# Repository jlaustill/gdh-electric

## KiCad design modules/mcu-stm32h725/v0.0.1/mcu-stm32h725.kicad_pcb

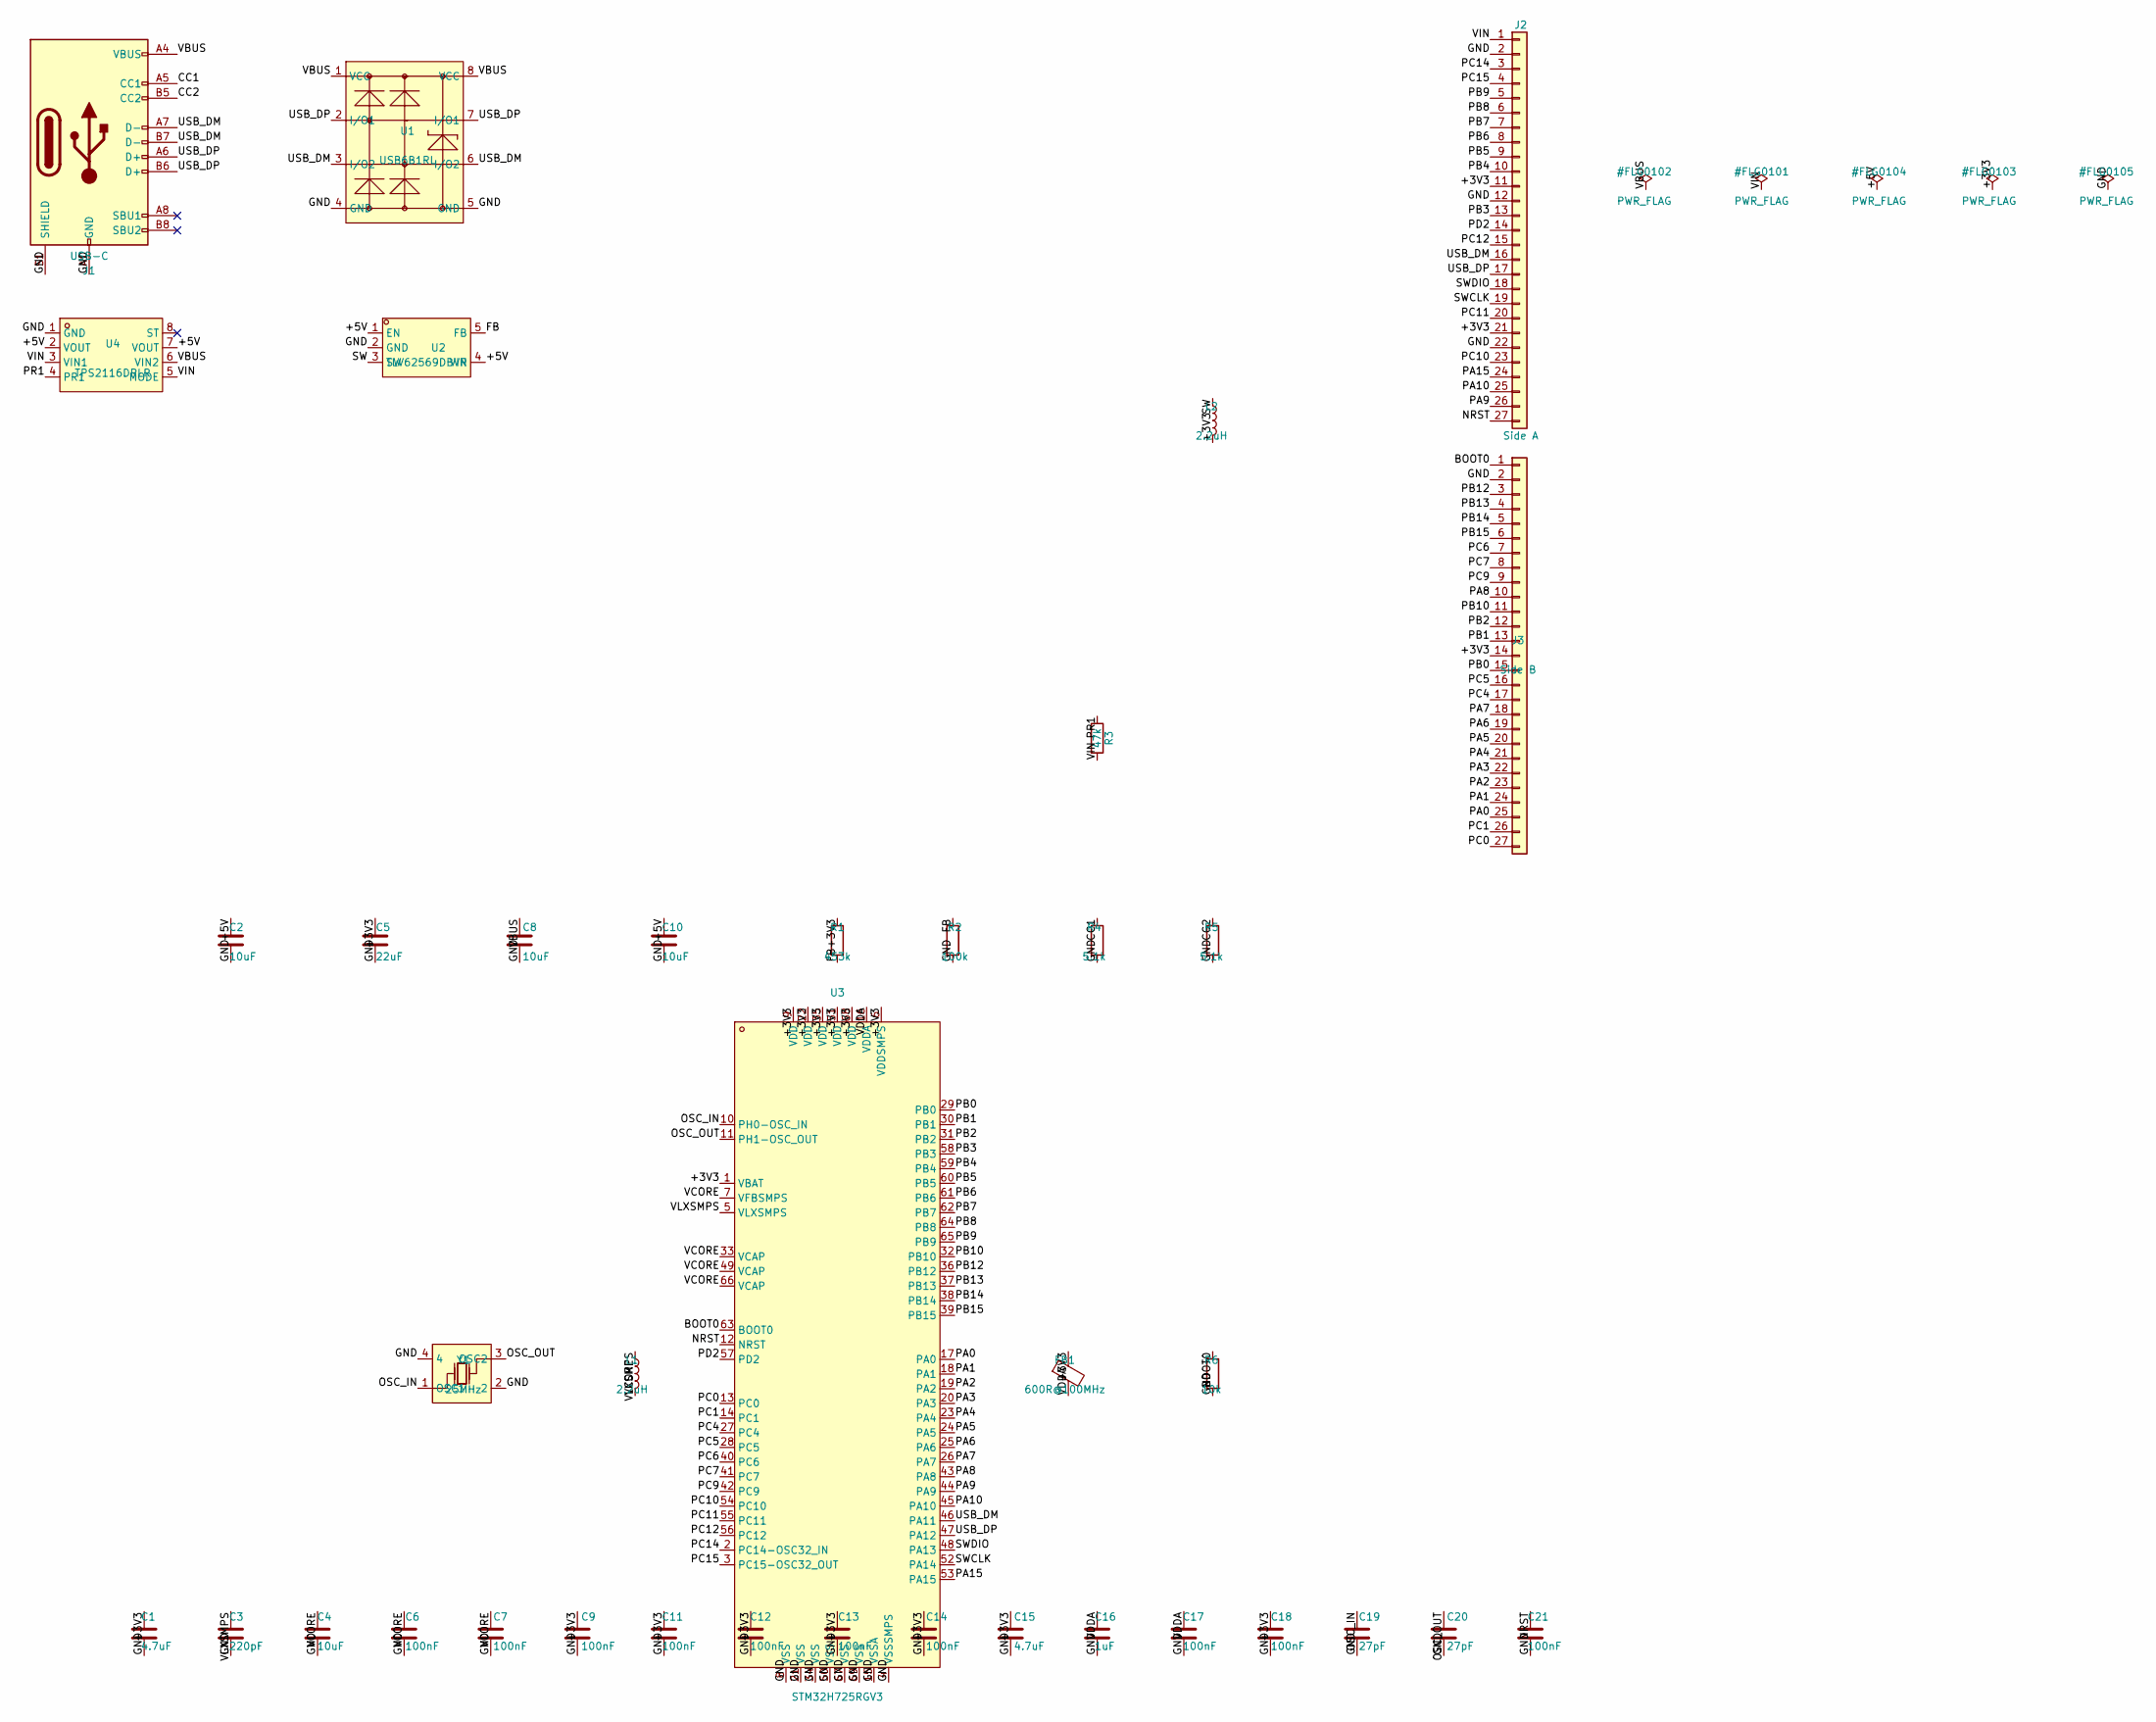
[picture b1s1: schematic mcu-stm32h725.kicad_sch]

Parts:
C1, C15: 4.7uF; C_0805_2012Metric
C2, C4, C8, C10: 10uF; C_0805_2012Metric
C3: 220pF; C_0402_1005Metric
C5: 22uF; C_0805_2012Metric
C6, C7, C9, C11, C12, C13, C14, C17, C18, C21: 100nF; C_0402_1005Metric
C16: 1uF; C_0805_2012Metric
C19, C20: 27pF; C_0402_1005Metric
FB1: 600R@100MHz; L_0805_2012Metric
J1: USB-C; USB-C_HYP_TC020-24LB02R_C23376530
J2: Side A; Castellation_1x27_P2.54mm_Edge
J3: Side B; Castellation_1x27_P2.54mm_Edge
L1, L2: 2.2uH; L_1210_3225Metric
R1: 453k; R_0603_1608Metric
R2: 100k; R_0603_1608Metric
R3: 47k; R_0603_1608Metric
R4, R5: 5.1k; R_0603_1608Metric
R6: 10k; R_0603_1608Metric
U1: USB6B1RL; SOIC-8_L4.9-W3.9-P1.27-LS6.0-BL
U2: TLV62569DBVR; SOT-23-5_L3.0-W1.7-P0.95-LS2.8-BR
U3: STM32H725RGV3; QFN-68_L8.0-W8.0-P0.40-BL-EP6.4
U4: TPS2116DRLR; SOT-583-8_L2.1-W1.6-P0.50-LS1.6-BL
Y1: 25MHz; CRYSTAL-SMD_4P-L3.2-W2.5-BL

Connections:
/+3V3: C1.1, C5.1, C9.1, C11.1, C12.1, C13.1, C14.1, C15.1, C18.1, FB1.1, J2.11, J2.21, J3.14, L2.2, R1.1, U3.1 (VBAT), U3.6 (VDDSMPS), U3.9 (VDD), U3.22 (VDD), U3.35 (VDD), U3.51 (VDD), U3.68 (VDD)
/+5V: C2.1, C10.1, U2.1 (EN), U2.4 (VIN), U4.2 (VOUT), U4.7 (VOUT)
/BOOT0: J3.1, R6.1, U3.63 (BOOT0)
/CC1: J1.A5 (CC1), R4.1
/CC2: J1.B5 (CC2), R5.1
/FB: R1.2, R2.1, U2.5 (FB)
/GND: C1.2, C2.2, C3.2, C4.2, C5.2, C6.2, C7.2, C8.2, C9.2, C10.2, C11.2, C12.2, C13.2, C14.2, C15.2, C16.2, C17.2, C18.2, C19.2, C20.2, C21.2, J1.A1 (GND), J1.A12 (GND), J1.B1 (GND), J1.B12 (GND), J1.S1 (SHIELD), J2.2, J2.12, J2.22, J3.2, R2.2, R4.2, R5.2, R6.2, U1.4 (GND), U1.5 (GND), U2.2 (GND), U3.4 (VSSSMPS), U3.8 (VSS), U3.15 (VSSA), U3.21 (VSS), U3.34 (VSS), U3.50 (VSS), U3.67 (VSS), U3.69 (VSS), U4.1 (GND), Y1.2, Y1.4
/NRST: C21.1, J2.27, U3.12 (NRST)
/OSC_IN: C19.1, U3.10 (PH0-OSC_IN), Y1.1 (OSC1)
/OSC_OUT: C20.1, U3.11 (PH1-OSC_OUT), Y1.3 (OSC2)
/PA0: J3.25, U3.17 (PA0)
/PA1: J3.24, U3.18 (PA1)
/PA2: J3.23, U3.19 (PA2)
/PA3: J3.22, U3.20 (PA3)
/PA4: J3.21, U3.23 (PA4)
/PA5: J3.20, U3.24 (PA5)
/PA6: J3.19, U3.25 (PA6)
/PA7: J3.18, U3.26 (PA7)
/PA8: J3.10, U3.43 (PA8)
/PA9: J2.26, U3.44 (PA9)
/PA10: J2.25, U3.45 (PA10)
/PA15: J2.24, U3.53 (PA15)
/PB0: J3.15, U3.29 (PB0)
/PB1: J3.13, U3.30 (PB1)
/PB2: J3.12, U3.31 (PB2)
/PB3: J2.13, U3.58 (PB3)
/PB4: J2.10, U3.59 (PB4)
/PB5: J2.9, U3.60 (PB5)
/PB6: J2.8, U3.61 (PB6)
/PB7: J2.7, U3.62 (PB7)
/PB8: J2.6, U3.64 (PB8)
/PB9: J2.5, U3.65 (PB9)
/PB10: J3.11, U3.32 (PB10)
/PB12: J3.3, U3.36 (PB12)
/PB13: J3.4, U3.37 (PB13)
/PB14: J3.5, U3.38 (PB14)
/PB15: J3.6, U3.39 (PB15)
/PC0: J3.27, U3.13 (PC0)
/PC1: J3.26, U3.14 (PC1)
/PC4: J3.17, U3.27 (PC4)
/PC5: J3.16, U3.28 (PC5)
/PC6: J3.7, U3.40 (PC6)
/PC7: J3.8, U3.41 (PC7)
/PC9: J3.9, U3.42 (PC9)
/PC10: J2.23, U3.54 (PC10)
/PC11: J2.20, U3.55 (PC11)
/PC12: J2.15, U3.56 (PC12)
/PC14: J2.3, U3.2 (PC14-OSC32_IN)
/PC15: J2.4, U3.3 (PC15-OSC32_OUT)
/PD2: J2.14, U3.57 (PD2)
/PR1: R3.1, U4.4 (PR1)
/SW: L2.1, U2.3 (SW)
/SWCLK: J2.19, U3.52 (PA14)
/SWDIO: J2.18, U3.48 (PA13)
/USB_DM: J1.A7 (D-), J1.B7 (D-), J2.16, U1.3 (I/O2), U1.6 (I/O2), U3.46 (PA11)
/USB_DP: J1.A6 (D+), J1.B6 (D+), J2.17, U1.2 (I/O1), U1.7 (I/O1), U3.47 (PA12)
/VBUS: C8.1, J1.A4 (VBUS), J1.A9 (VBUS), J1.B4 (VBUS), J1.B9 (VBUS), U1.1 (VCC), U1.8 (VCC), U4.6 (VIN2)
/VCORE: C4.1, C6.1, C7.1, L1.2, U3.7 (VFBSMPS), U3.33 (VCAP), U3.49 (VCAP), U3.66 (VCAP)
/VDDA: C16.1, C17.1, FB1.2, U3.16 (VDDA)
/VIN: J2.1, R3.2, U4.3 (VIN1), U4.5 (MODE)
/VLXSMPS: C3.1, L1.1, U3.5 (VLXSMPS)

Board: 4 copper layers, 38 parts (0 on the bottom side), 61 nets, no tracks yet.
